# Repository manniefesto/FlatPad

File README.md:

# FlatPad

A 4x4 macro with promicro, rotary encoder and led backlighting, inspired by the Plaid and Zen keyboards.

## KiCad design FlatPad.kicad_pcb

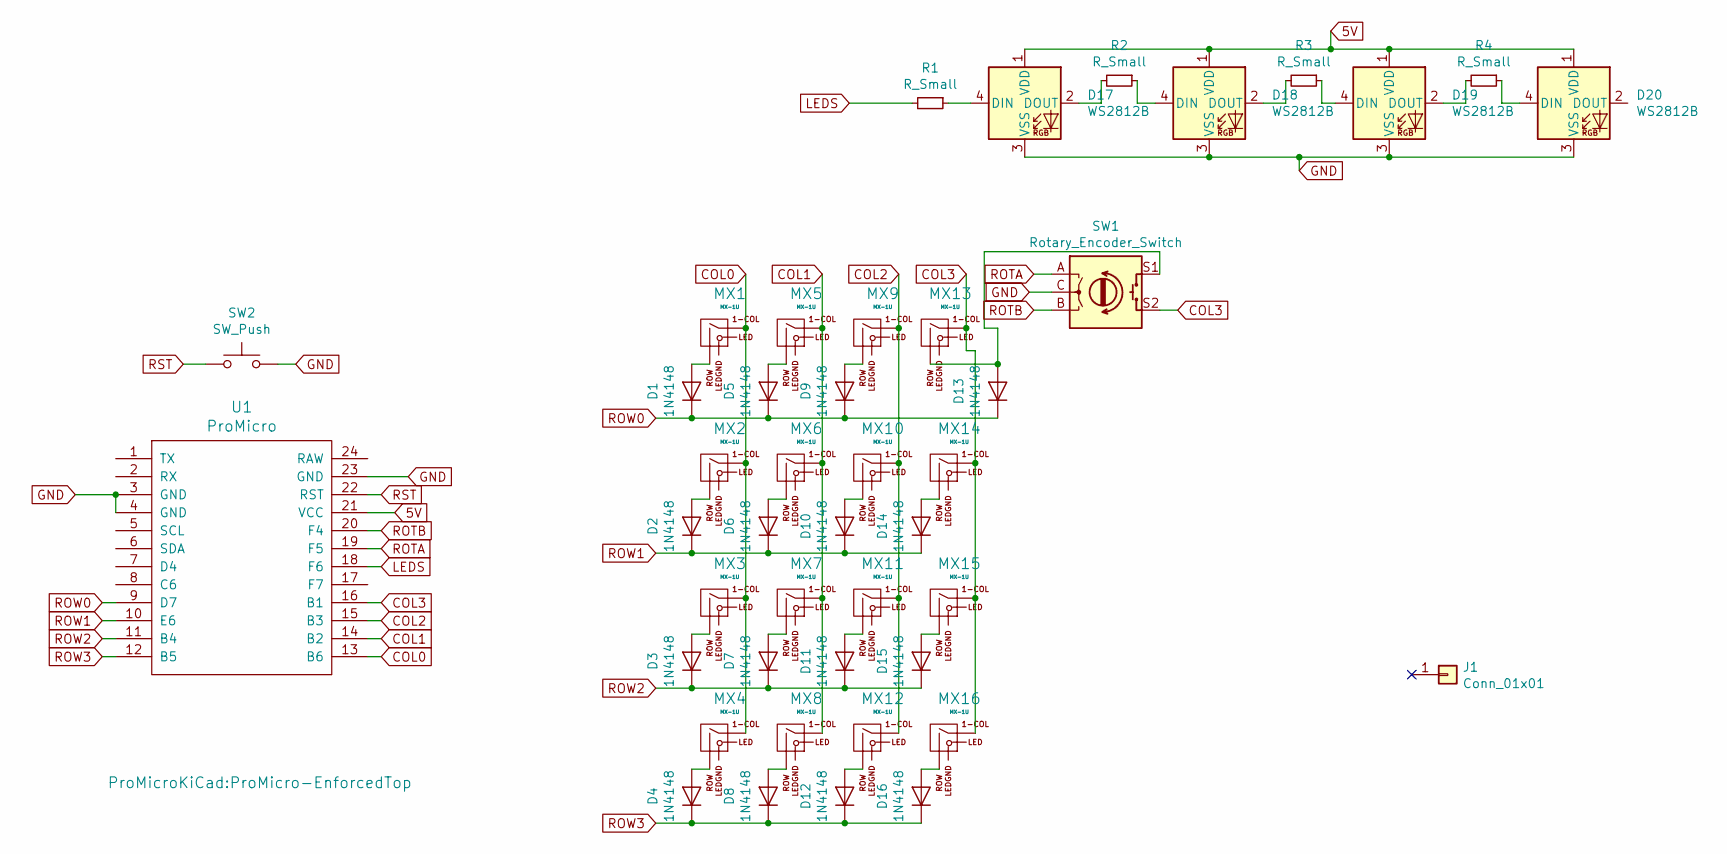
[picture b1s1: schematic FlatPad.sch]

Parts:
D1, D2, D3, D4, D5, D6, D7, D8, D9, D10, D11, D12, D13, D14, D15, D16: 1N4148; D_DO-35_SOD27_P7.62mm_Horizontal
D17, D18, D19, D20: WS2812B; LED_WS2812B_PLCC4_5.0x5.0mm_P3.2mm
J1: Conn_01x01; breakaway-mousebites
MX1, MX2, MX3, MX4, MX5, MX6, MX7, MX8, MX9, MX10, MX11, MX12, MX13, MX14, MX15, MX16: MX-1U
R1, R2, R3, R4: R_Small; R_0805_2012Metric_Pad1.15x1.40mm_HandSolder
SW1: Rotary_Encoder_Switch; RotaryEncoder_Alps_EC11E-Switch_Vertical_H20mm
SW2: SW_Push; PushButton_6x6mm_TH_Pretty
U1: ProMicro; ProMicro-EnforcedTop

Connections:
5V: D17.1 (VDD), D18.1 (VDD), D19.1 (VDD), D20.1 (VDD), U1.21 (VCC)
COL0: MX1.1 (COL), MX2.1 (COL), MX3.1 (COL), MX4.1 (COL), U1.13 (B6)
COL1: MX5.1 (COL), MX6.1 (COL), MX7.1 (COL), MX8.1 (COL), U1.14 (B2)
COL2: MX9.1 (COL), MX10.1 (COL), MX11.1 (COL), MX12.1 (COL), U1.15 (B3)
COL3: MX13.1 (COL), MX14.1 (COL), MX15.1 (COL), MX16.1 (COL), SW1.S2, U1.16 (B1)
GND: D17.3 (VSS), D18.3 (VSS), D19.3 (VSS), D20.3 (VSS), SW1.C, SW2.2, U1.3 (GND), U1.4 (GND), U1.23 (GND)
LEDS: R1.2, U1.18 (F6)
unnamed: D1.2 (A), MX1.2 (ROW)
unnamed: D2.2 (A), MX2.2 (ROW)
unnamed: D3.2 (A), MX3.2 (ROW)
unnamed: D4.2 (A), MX4.2 (ROW)
unnamed: D5.2 (A), MX5.2 (ROW)
unnamed: D6.2 (A), MX6.2 (ROW)
unnamed: D7.2 (A), MX7.2 (ROW)
unnamed: D8.2 (A), MX8.2 (ROW)
unnamed: D9.2 (A), MX9.2 (ROW)
unnamed: D10.2 (A), MX10.2 (ROW)
unnamed: D11.2 (A), MX11.2 (ROW)
unnamed: D12.2 (A), MX12.2 (ROW)
unnamed: D13.2 (A), MX13.2 (ROW), SW1.S1
unnamed: D14.2 (A), MX14.2 (ROW)
unnamed: D15.2 (A), MX15.2 (ROW)
unnamed: D16.2 (A), MX16.2 (ROW)
unnamed: D17.2 (DOUT), R2.2
unnamed: D17.4 (DIN), R1.1
unnamed: D18.2 (DOUT), R3.2
unnamed: D18.4 (DIN), R2.1
unnamed: D19.2 (DOUT), R4.2
unnamed: D19.4 (DIN), R3.1
unnamed: D20.4 (DIN), R4.1
ROTA: SW1.A, U1.19 (F5)
ROTB: SW1.B, U1.20 (F4)
ROW0: D1.1 (K), D5.1 (K), D9.1 (K), D13.1 (K), U1.9 (D7)
ROW1: D2.1 (K), D6.1 (K), D10.1 (K), D14.1 (K), U1.10 (E6)
ROW2: D3.1 (K), D7.1 (K), D11.1 (K), D15.1 (K), U1.11 (B4)
ROW3: D4.1 (K), D8.1 (K), D12.1 (K), D16.1 (K), U1.12 (B5)
RST: SW2.1, U1.22 (RST)

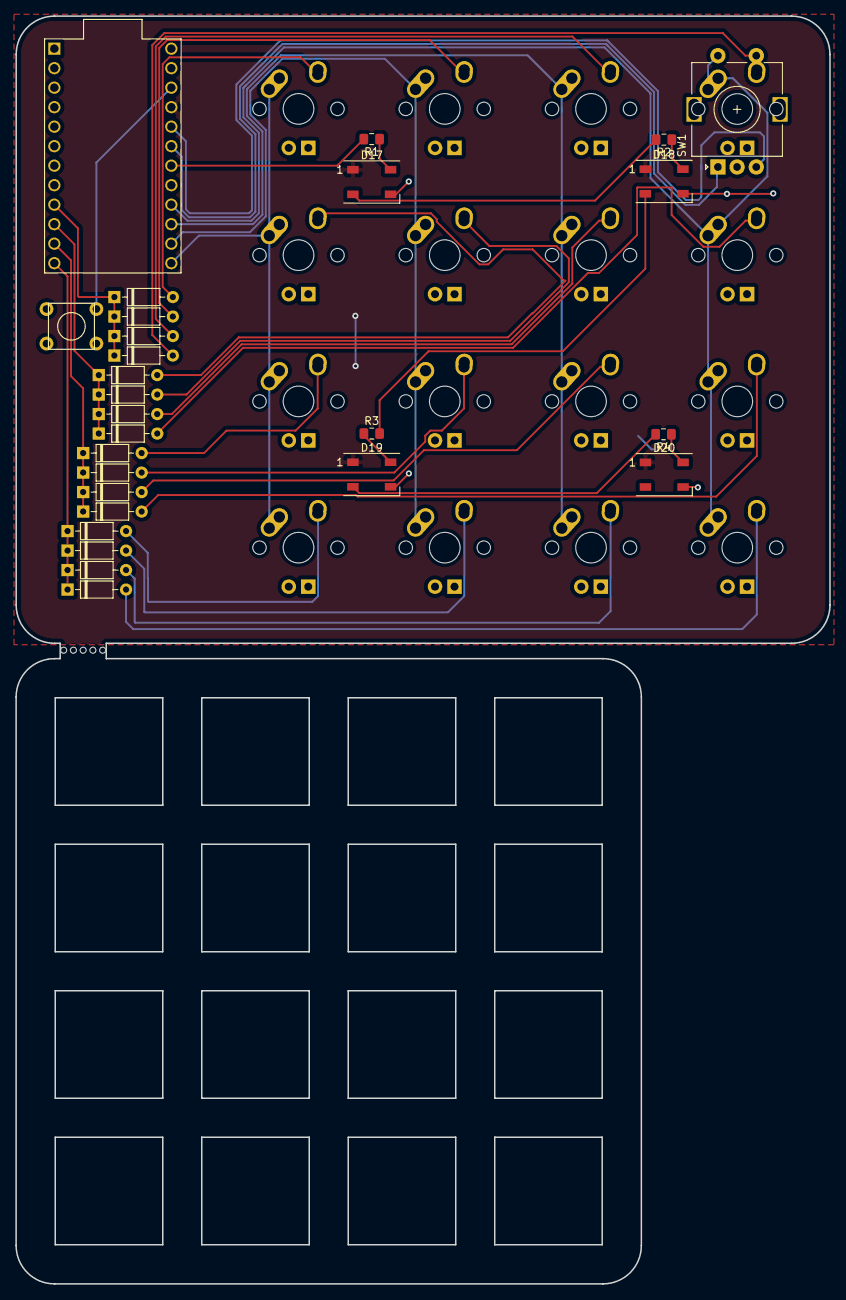
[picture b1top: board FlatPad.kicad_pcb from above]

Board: 2 copper layers, 106.0 x 165.1 mm, 44 parts (0 on the bottom side), 37 nets.

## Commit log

2020-07-02 Init commit
2020-07-02 Added PCB render
2020-07-05 Added mx foot print to rotary encoder position
2020-07-05 Readme update
2020-07-07 Cleaned up MX/Rotary tracks
2020-07-07 Updated png
2020-07-08 rerouted ROTB track
